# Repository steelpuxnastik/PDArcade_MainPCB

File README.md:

# PCB mainboard (with changes) for a homemade arcade controller for Hatsune Miku Project DIVA Arcade Future Tone. Based on http://pol.dip.jp/diva/

First version (homemade)

First version (factory made)

In last commits it has some changes, most noticeable are holes for a 4,7k resistors for I2C connestion with CY8CKIT-049-4200 (I do not know why I didn't add it on the beginning) and visual changes (using a SilkS layers and ground mask). Also I added mounting holes for a DC/DC stepdown converter, it will be useful if you'll use 5V WS2812b LED strip, because LEDs in button use 12V, but strip 5V.

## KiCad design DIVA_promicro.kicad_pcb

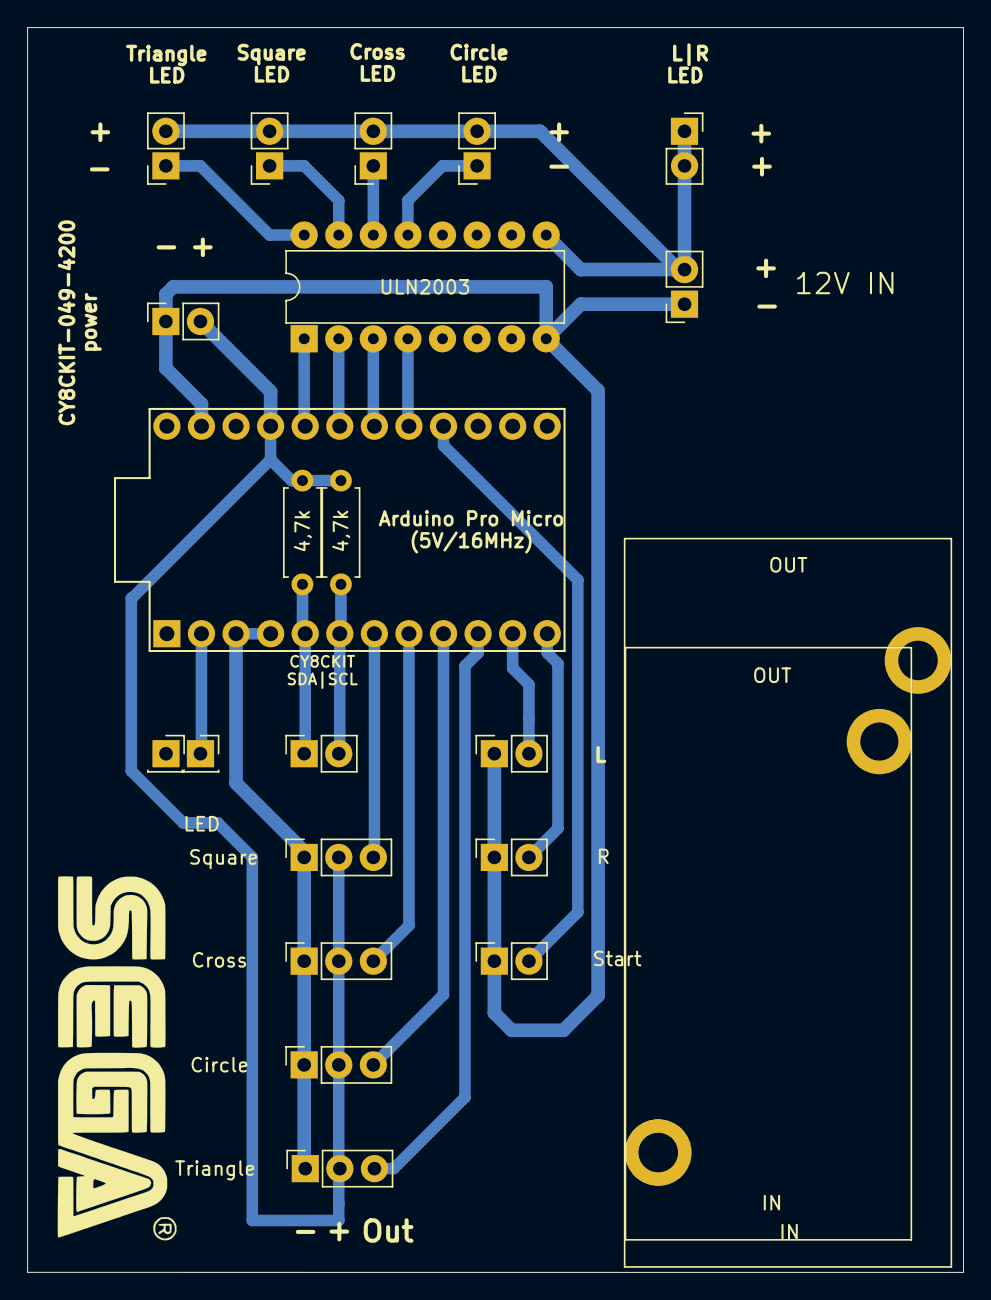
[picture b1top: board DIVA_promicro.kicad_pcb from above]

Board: 2 copper layers, 68.8 x 91.4 mm, 21 parts (0 on the bottom side), 21 nets.

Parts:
4,7k, 4,7k#2: 4,7К; R_Axial_DIN0207_L6.3mm_D2.5mm_P7.62mm_Horizontal
12V IN: 12V_IN; PinSocket_1x02_P2.54mm_Vertical
CIRCLE_LED1: CIRCLE_LED_Conn_01x02; PinSocket_1x02_P2.54mm_Vertical
CROSS_LED1: CROSS_LED_Conn_01x02; PinSocket_1x02_P2.54mm_Vertical
CY8CKIT SDA|SCL: I2C_Conn_01x02; PinSocket_1x02_P2.54mm_Vertical
Circle: CIRCLE_Conn_01x03; PinSocket_1x03_P2.54mm_Vertical
Cross: CROSS_Conn_01x03; PinSocket_1x03_P2.54mm_Vertical
CypressPower1: PowerToCypress_Conn_01x02; PinSocket_1x02_P2.54mm_Vertical
L: L_Button_Conn_01x02; PinSocket_1x02_P2.54mm_Vertical
L/R_LED1: LR_LED_Conn_01x02; PinSocket_1x02_P2.54mm_Vertical
LED, LED1: LED_Strip_Conn_01x01; PinSocket_1x01_P2.54mm_Vertical
ProMicro1: ProMicro
R: R_Button_Conn_01x02; PinSocket_1x02_P2.54mm_Vertical
SQUARE_LED1: SQUARE_LED_Conn_01x02; PinSocket_1x02_P2.54mm_Vertical
Square: SQUARE_Conn_01x03; PinSocket_1x03_P2.54mm_Vertical
Start: START_Conn_01x02; PinSocket_1x02_P2.54mm_Vertical
TRIANGLE_LED1: TRIANGLE_LED_Conn_01x02; PinSocket_1x02_P2.54mm_Vertical
Triangle: TRIANGLE_Conn_01x03; PinSocket_1x03_P2.54mm_Vertical
ULN2003: ULN2003; DIP-16_W7.62mm

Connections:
unnamed: 12V IN.1, Circle.1, Cross.1, CypressPower1.1, L.1, ProMicro1.3, ProMicro1.4, ProMicro1.23, R.1, Square.1, Start.1, Triangle.1, ULN2003.8
unnamed: 4,7k.1, 4,7k#2.1, Circle.2, Cross.2, CypressPower1.2, ProMicro1.21, Square.2, Triangle.2
unnamed: ProMicro1.10, Triangle.3
unnamed: Circle.3, ProMicro1.9
unnamed: Cross.3, ProMicro1.8
unnamed: ProMicro1.12, R.2
unnamed: ProMicro1.7, Square.3
unnamed: L.2, ProMicro1.11
unnamed: LED.1, LED1.1, ProMicro1.2
unnamed: 4,7k#2.2, CY8CKIT SDA|SCL.1, ProMicro1.5
unnamed: 4,7k.2, CY8CKIT SDA|SCL.2, ProMicro1.6
unnamed: ProMicro1.16, Start.2
unnamed: TRIANGLE_LED1.1, ULN2003.16
unnamed: 12V IN.2, CIRCLE_LED1.2, CROSS_LED1.2, L/R_LED1.1, L/R_LED1.2, SQUARE_LED1.2, TRIANGLE_LED1.2, ULN2003.9
unnamed: SQUARE_LED1.1, ULN2003.15
unnamed: CROSS_LED1.1, ULN2003.14
unnamed: CIRCLE_LED1.1, ULN2003.13
unnamed: ProMicro1.17, ULN2003.4
unnamed: ProMicro1.18, ULN2003.3
unnamed: ProMicro1.19, ULN2003.2
unnamed: ProMicro1.20, ULN2003.1

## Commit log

2019-11-27 Final board
2019-12-11 Added mounting holes for resistors
    Added mounting holes for two 4,7K resistors that used in I2C connection
2020-01-04 images
2020-01-05 images + visual pcb changes
2020-01-05 Added mounting holes for a DC/DC step-down modules
    Added mounting holes for a DC/DC step-down modules XL4015 (bigger) and LM2596S (smaller) if you will install 5V WS2812B LED strip. But footprints for them need to be confirmed.
2020-02-10 Added resistor for a LED strip signal line
